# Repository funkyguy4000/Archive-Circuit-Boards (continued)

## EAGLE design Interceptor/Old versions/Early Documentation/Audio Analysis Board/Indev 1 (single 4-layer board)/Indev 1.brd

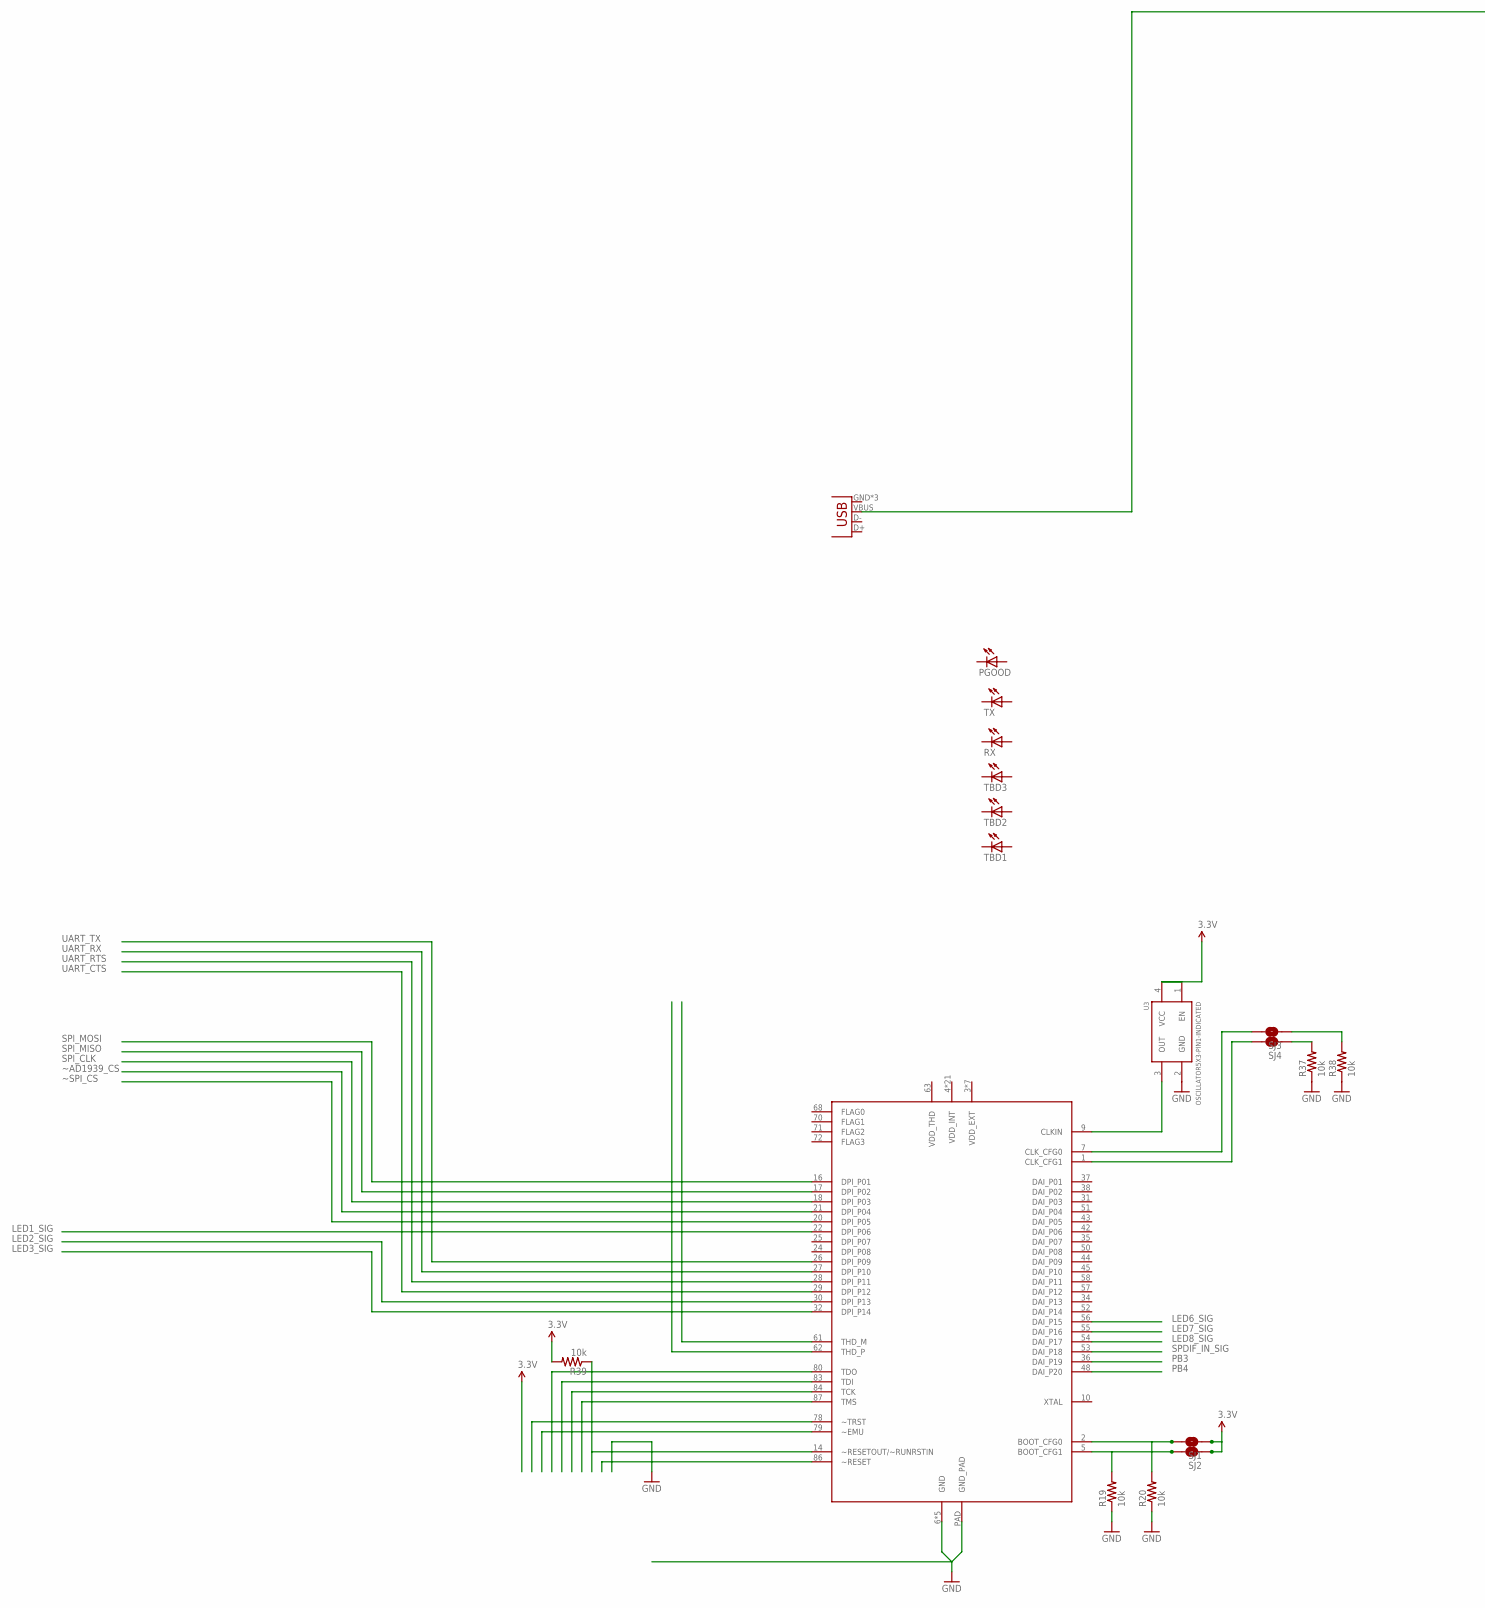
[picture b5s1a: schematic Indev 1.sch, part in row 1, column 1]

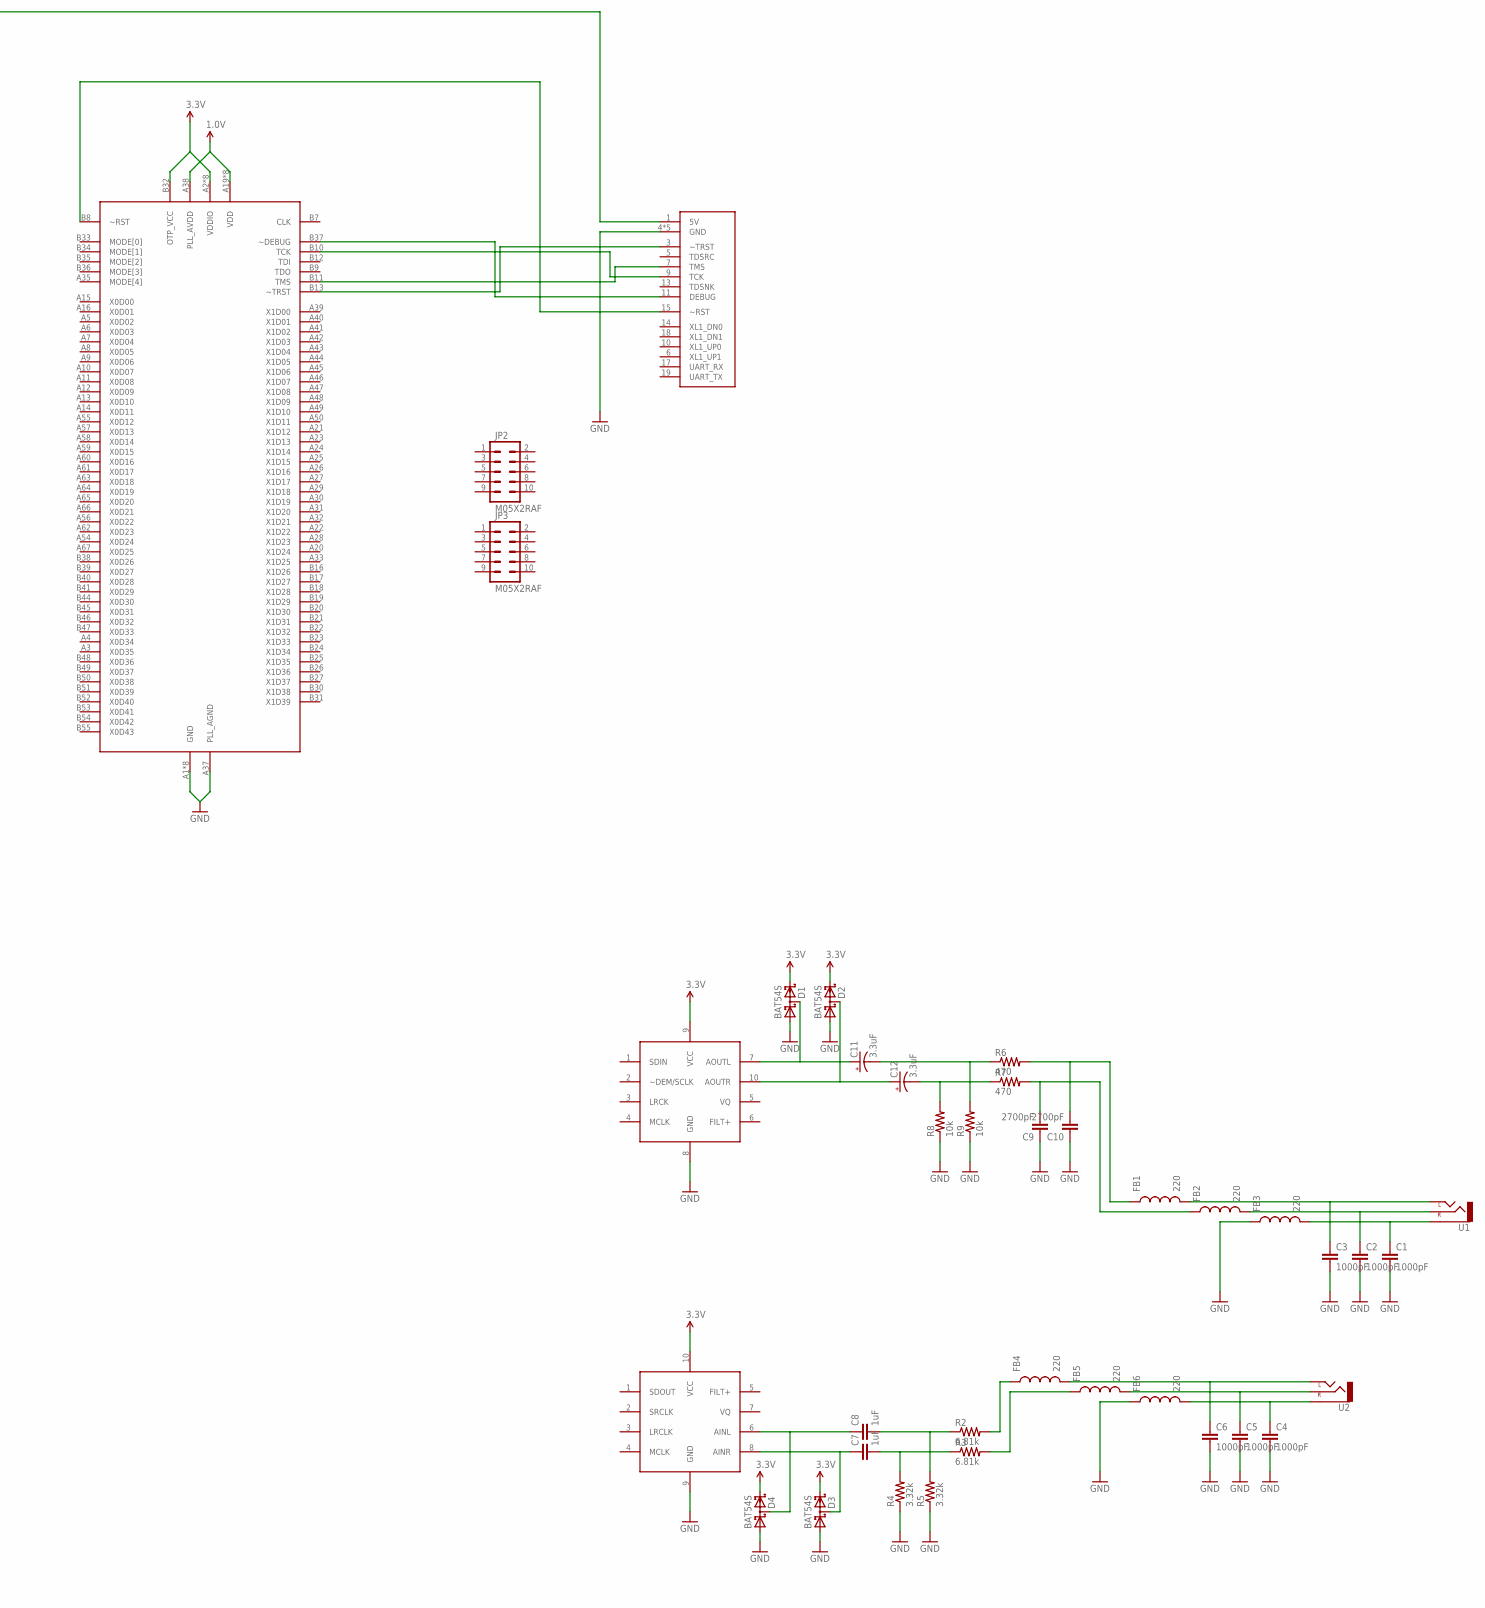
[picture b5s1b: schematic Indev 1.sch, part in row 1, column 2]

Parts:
C1, C2, C3, C4, C5, C6: 1000pF; 0402-CAP
C7, C8: 1uF; 0402-CAP
C9, C10: 2700pF; 0402-CAP
C11, C12: 3.3uF; EIA3216
D1, D2, D3, D4: BAT54S; SOT23
FB1, FB2, FB3, FB4, FB5, FB6: 220; 0805
JP1: USB-MICROB
JP2, JP3: M05X2RAF; 2X5-RAF
PGOOD: LEDCHIP-LED0603; CHIP-LED0603
R2, R3: 6.81k; 0603-RES
R4, R5: 3.32k; 0603-RES
R6, R7: 470; 0603-RES
R8, R9, R19, R20, R37, R38, R39: 10k; 0603-RES
RX: LEDCHIP-LED0603; CHIP-LED0603
SJ1, SJ2, SJ3, SJ4: SOLDERJUMPERNC; SJ_2S
TBD1, TBD2, TBD3: LEDCHIP-LED0603; CHIP-LED0603
TX: LEDCHIP-LED0603; CHIP-LED0603
U1, U2: AUDIO-JACKSMD2; AUDIO-JACK-3.5MM-SMD
U3: OSCILLATOR5X3-PIN1-INDICATED; CRYSTAL-OSC-SMD-5X3
U$1: ADSP-21479; QFN-88
U$2: CS4344-DAC; TSSOP-10
U$3: CS5343; TSSOP-10
U$4: XTAG-2; MOLEX-52745-2097
U$6: XS1-L8A-128-QF124; QFN-124

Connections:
1.0V: U$6.A19 (VDD), U$6.A34 (VDD), U$6.A38 (PLL_AVDD), U$6.A53 (VDD), U$6.A68 (VDD), U$6.B15 (VDD), U$6.B28 (VDD), U$6.B43 (VDD), U$6.B56 (VDD)
3.3V: R39.2, SJ1.1, SJ2.1, U3.1 (EN), U3.4 (VCC), U$6.A2 (VDDIO), U$6.A17 (VDDIO), U$6.A36 (VDDIO), U$6.A51 (VDDIO), U$6.B1 (VDDIO), U$6.B14 (VDDIO), U$6.B29 (VDDIO), U$6.B32 (OTP_VCC), U$6.B42 (VDDIO)
AINL: C6.1, FB4.2, U2.TIP (LEFT)
AINL_C: C8.1, D4.3 (C1A2), U$3.6 (AINL)
AINL_FB: FB4.1, R2.2
AINL_R: C8.2, R2.1, R5.2
AINR: C5.1, FB5.2, U2.RING (RIGHT)
AINR_C: C7.1, D3.3 (C1A2), U$3.8 (AINR)
AINR_FB: FB5.1, R3.2
AINR_R: C7.2, R3.1, R4.2
AIN_SLEEV: C4.1, FB6.2, U2.SLEEVE
AOUTL: C3.1, FB1.2, U1.TIP (LEFT)
AOUTL_C: C11.A (+), D1.3 (C1A2), U$2.7 (AOUTL)
AOUTL_FB: C10.2, FB1.1, R6.2
AOUTL_R: C11.C (-), R6.1, R9.2
AOUTR: C2.1, FB2.2, U1.RING (RIGHT)
AOUTR_C: C12.A (+), D2.3 (C1A2), U$2.10 (AOUTR)
AOUTR_FB: C9.2, FB2.1, R7.2
AOUTR_R: C12.C (-), R7.1, R8.2
AOUTS: C1.1, FB3.2, U1.SLEEVE
GND: C1.2, C2.2, C3.2, C4.2, C5.2, C6.2, C9.1, C10.1, D1.1 (A1), D2.1 (A1), D3.1 (A1), D4.1 (A1), FB3.1, FB6.1, R4.1, R5.1, R8.1, R9.1, R19.1, R20.1, R37.1, R38.1, U3.2 (GND), U$1.6 (GND), U$1.60 (GND), U$1.73 (GND), U$1.74 (GND), U$1.76 (GND), U$1.PAD (GND_PAD), U$2.8 (GND), U$3.9 (GND), U$4.4 (GND), U$4.8 (GND), U$4.12 (GND), U$4.16 (GND), U$4.20 (GND), U$6.A1 (GND), U$6.A18 (GND), U$6.A37 (PLL_AGND), U$6.A52 (GND), U$6.B2 (GND), U$6.B4 (GND), U$6.B5 (GND), U$6.B6 (GND), U$6.PAD (GND)
LED1_SIG: U$1.22 (DPI_P06)
LED2_SIG: U$1.30 (DPI_P13)
LED3_SIG: U$1.32 (DPI_P14)
LED6_SIG: U$1.56 (DAI_P15)
LED7_SIG: U$1.55 (DAI_P16)
LED8_SIG: U$1.54 (DAI_P17)
unnamed: JP1.VBUS, U$4.1 (5V)
unnamed: U$4.11 (DEBUG), U$6.B37 (~DEBUG)
unnamed: U3.3 (OUT), U$1.9 (CLKIN)
unnamed: U$4.9 (TCK), U$6.B10 (TCK)
unnamed: U$4.7 (TMS), U$6.B11 (TMS)
unnamed: SJ3.2, U$1.7 (CLK_CFG0)
unnamed: SJ4.2, U$1.1 (CLK_CFG1)
unnamed: R37.2, SJ4.1
unnamed: U$4.3 (~TRST), U$6.B13 (~TRST)
unnamed: R38.2, SJ3.1
unnamed: U$4.15 (~RST), U$6.B8 (~RST)
unnamed: R20.2, SJ1.2, U$1.2 (BOOT_CFG0)
unnamed: R39.1, U$1.14 (~RESETOUT/~RUNRSTIN)
unnamed: R19.2, SJ2.2, U$1.5 (BOOT_CFG1)
PB3: U$1.36 (DAI_P19)
PB4: U$1.48 (DAI_P20)
SPDIF_IN_SIG: U$1.53 (DAI_P18)
SPI_CLK: U$1.18 (DPI_P03)
SPI_MISO: U$1.17 (DPI_P02)
SPI_MOSI: U$1.16 (DPI_P01)
UART_CTS: U$1.29 (DPI_P12)
UART_RTS: U$1.28 (DPI_P11)
UART_RX: U$1.27 (DPI_P10)
UART_TX: U$1.26 (DPI_P09)
VCC: D1.2 (C2), D2.2 (C2), D3.2 (C2), D4.2 (C2), U$2.9 (VCC), U$3.10 (VCC)
~AD1939_CS: U$1.21 (DPI_P04)
~SPI_CS: U$1.20 (DPI_P05)

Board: 4 copper layers, 56 parts (8 on the bottom side), 36 nets, no tracks yet.

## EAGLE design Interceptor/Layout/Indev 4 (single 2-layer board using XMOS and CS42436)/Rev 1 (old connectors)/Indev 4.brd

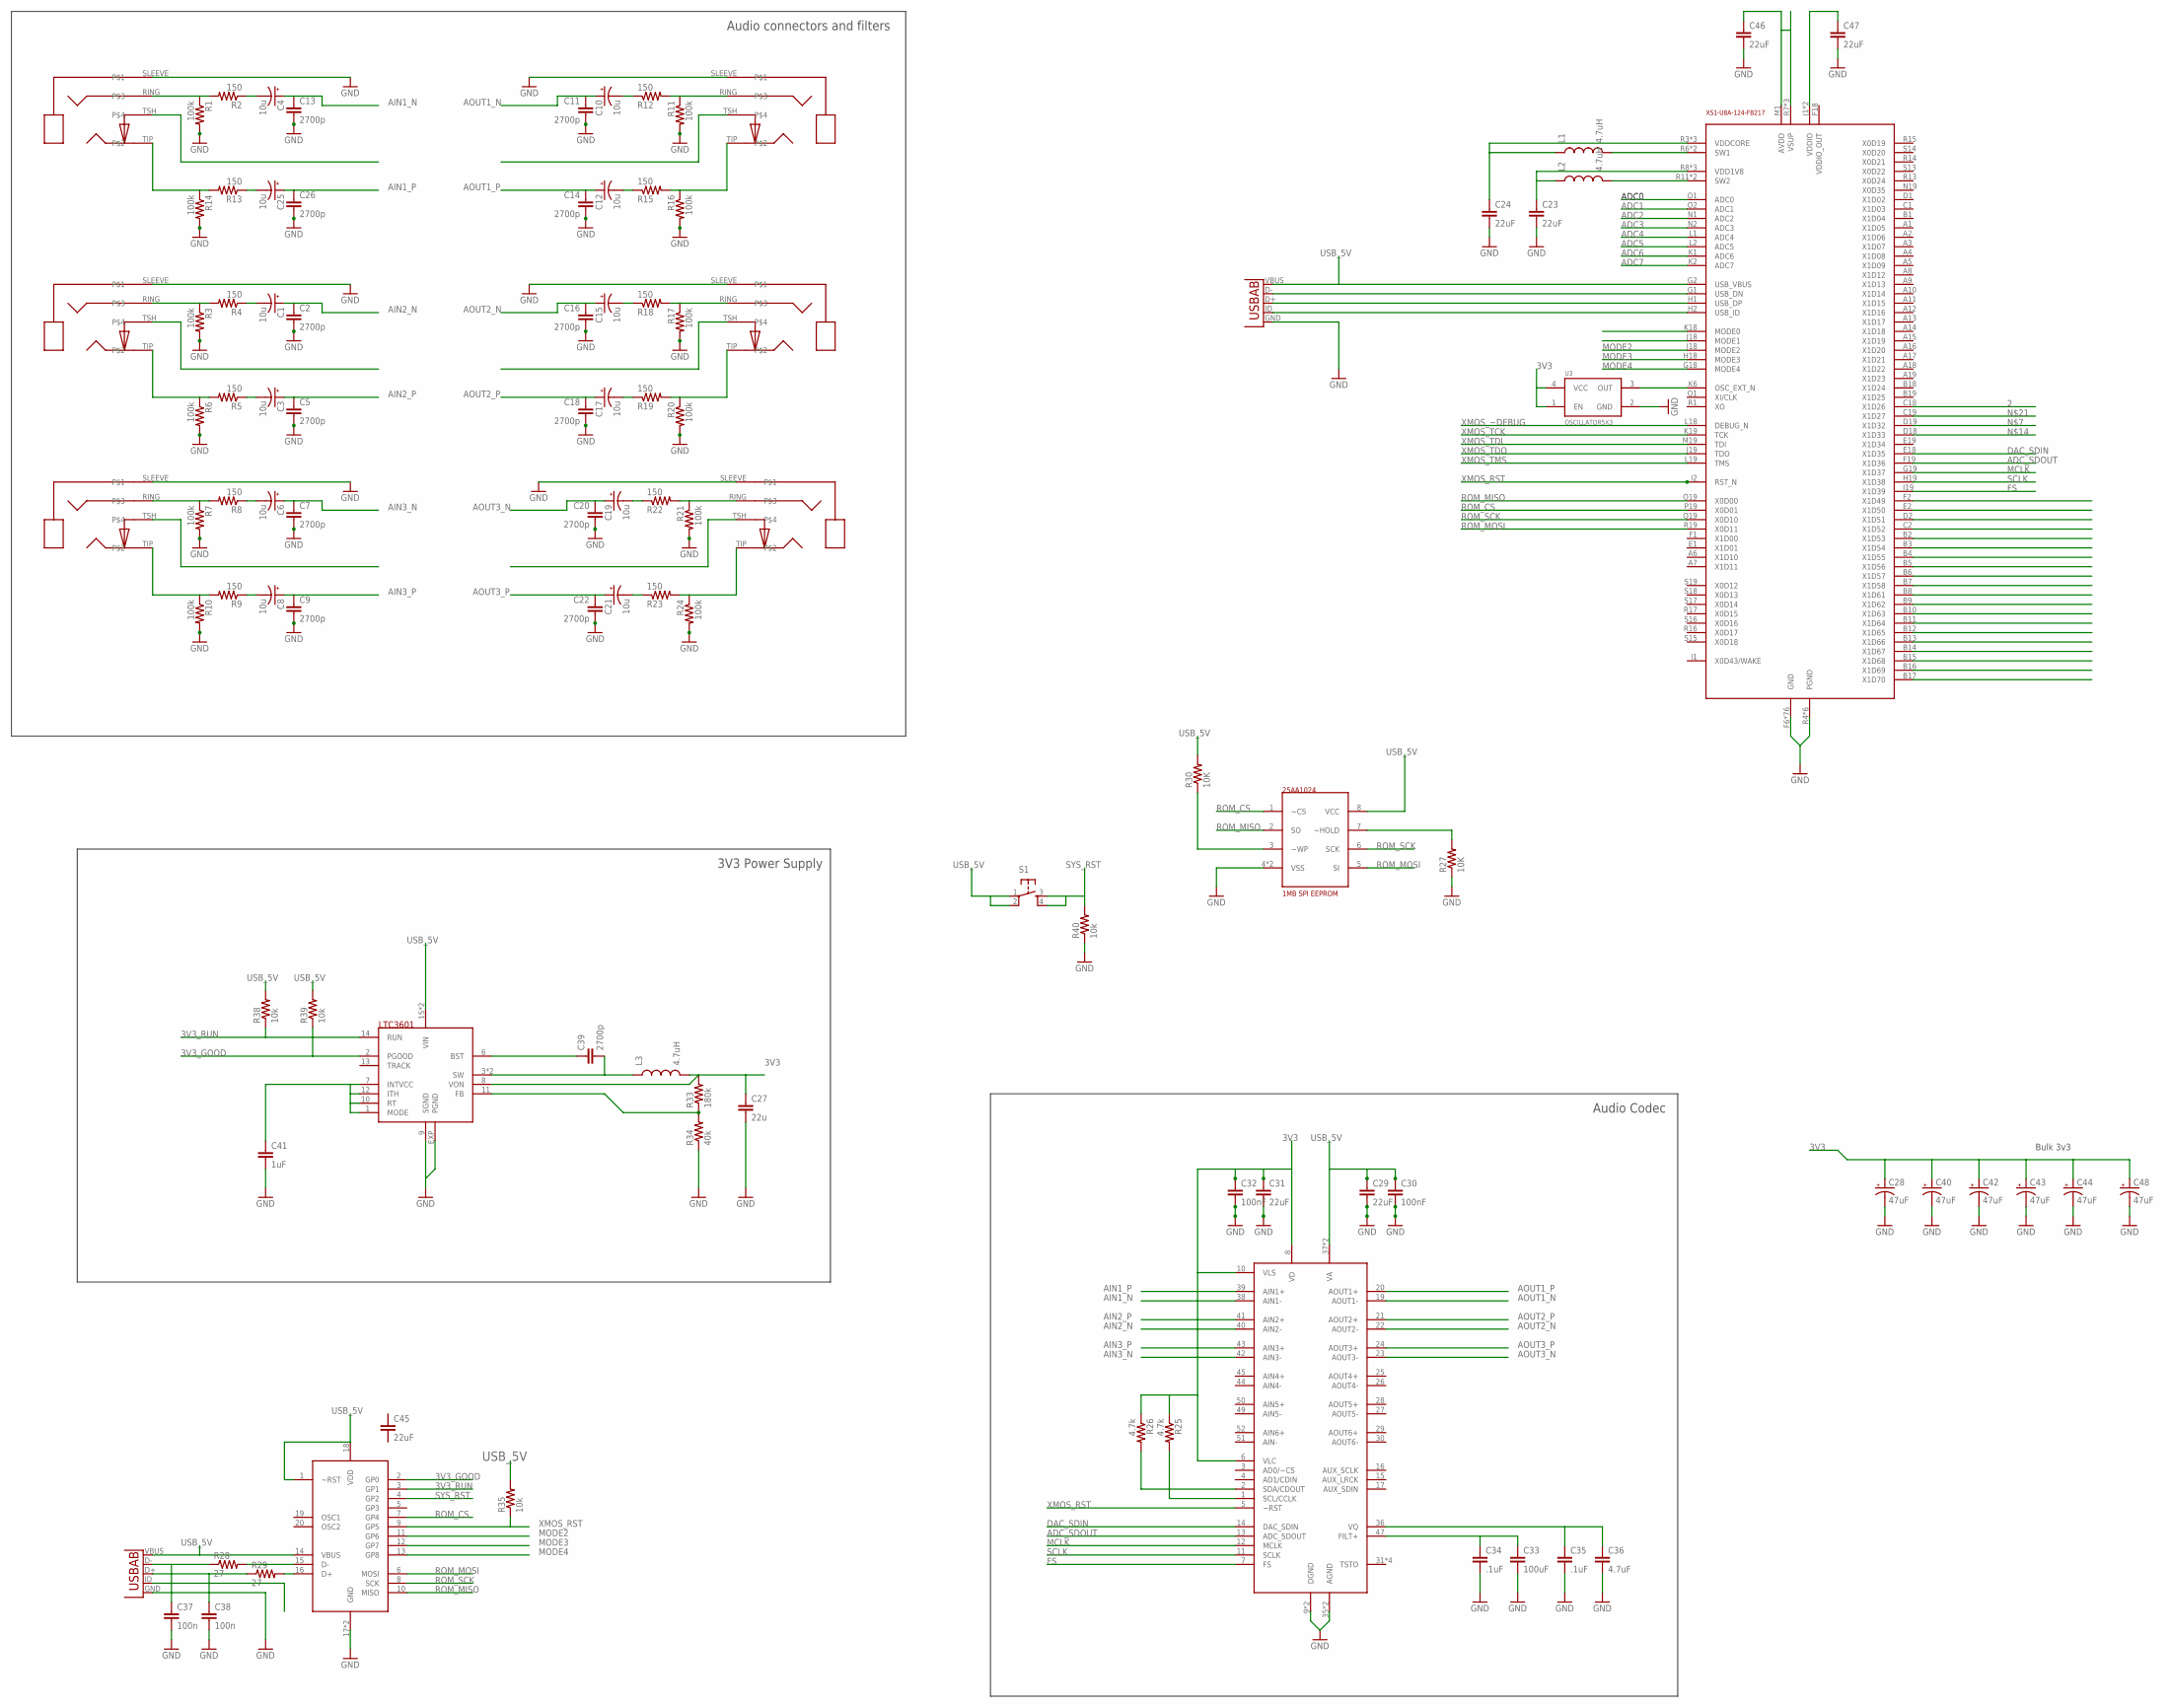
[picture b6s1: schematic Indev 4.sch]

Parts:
C1, C3, C4, C6, C8, C10, C12, C15, C17, C19, C21, C25: 10u; PANASONIC_B
C2, C5, C7, C9, C11, C13, C14, C16, C18, C20, C22, C26, C39: 2700p; 0603-CAP
C23, C24: 22uF; 0603-CAP
C27: 22u; 0603-CAP
C28, C40, C42, C43, C44, C48: 47uF; EIA3528
C29, C31, C45, C46, C47: 22uF; 0402-CAP
C30, C32: 100nF; 0402-CAP
C33: 100uF; 0402-CAP
C34, C35: .1uF; 0402-CAP
C36: 4.7uF; 0402-CAP
C37, C38: 100n; 0603-CAP
C41: 1uF; 0603-CAP
J1, J2, J3, J4, J5, J6: SJ3524_AUDIO
L1, L2, L3: 4.7uH; 1210
R1, R3, R6, R7, R10, R11, R14, R16, R17, R20, R21, R24: 100k; R0402
R2, R4, R5, R8, R9, R12, R13, R15, R18, R19, R22, R23: 150; R0402
R25, R26: 4.7k; R0402
R27, R30: 10K; R0402
R28, R29: 27; R0402
R33: 180k; R0402
R34: 40k; R0402
R35, R38, R39, R40: 10k; R0402
S1: TAC_SWITCHSMD; TACTILE_SWITCH_SMD
U1, U2: USB-AB; USB-AB-MICRO-SMD
U3: OSCILLATOR5X3; CRYSTAL-SMD-5X3
U$1: LTC3601; QFN16-3X3
U$2: 25AA1024DFN; DFN8-5X6
U$3: CS42436; QFP-52
U$4: MCP2210QFN; 20-QFN(5X5)
U$6: XS1-U8A-124-FB217; 217-BGA(.8MM)

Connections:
2: U$6.C18 (X1D26)
3V3: C27.1, C28.A (+), C31.1, C32.1, C40.A (+), C42.A (+), C43.A (+), C44.A (+), C46.1, C47.1, C48.A (+), L3.2, R25.1, R26.1, R33.2, U3.1 (EN), U3.4 (VCC), U$1.8 (VON), U$3.6 (VLC), U$3.8 (VD), U$3.10 (VLS), U$6.J1 (VDDIO), U$6.J2 (VDDIO), U$6.M1 (AVDD), U$6.R7 (VSUP), U$6.S1 (VSUP), U$6.S7 (VSUP)
3V3_GOOD: R39.1, U$1.2 (PGOOD), U$4.2 (GP0)
3V3_RUN: R38.1, U$1.14 (RUN), U$4.3 (GP1)
ADC0: U$6.O1 (ADC0)
ADC1: U$6.O2 (ADC1)
ADC2: U$6.N1 (ADC2)
ADC3: U$6.N2 (ADC3)
ADC4: U$6.L1 (ADC4)
ADC5: U$6.L2 (ADC5)
ADC6: U$6.K1 (ADC6)
ADC7: U$6.K2 (ADC7)
ADC_SDOUT: U$3.13 (ADC_SDOUT), U$6.F19 (X1D36)
AIN1_N: C4.+, C13.1, U$3.38 (AIN1-)
AIN1_P: C25.+, C26.1, U$3.39 (AIN1+)
AIN2_N: C1.+, C2.1, U$3.40 (AIN2-)
AIN2_P: C3.+, C5.1, U$3.41 (AIN2+)
AIN3_N: C6.+, C7.1, U$3.42 (AIN3-)
AIN3_P: C8.+, C9.1, U$3.43 (AIN3+)
AOUT1_N: C10.+, C11.1, U$3.19 (AOUT1-)
AOUT1_P: C12.+, C14.1, U$3.20 (AOUT1+)
AOUT2_N: C15.+, C16.1, U$3.22 (AOUT2-)
AOUT2_P: C17.+, C18.1, U$3.21 (AOUT2+)
AOUT3_N: C19.+, C20.1, U$3.23 (AOUT3-)
AOUT3_P: C21.+, C22.1, U$3.24 (AOUT3+)
CH1O_IN: J4.TSH
CH1_IN: J1.TSH
CH2O_IN: J5.TSH
CH2_IN: J2.TSH
CH3O_IN: J6.TSH
CH3_IN: J3.TSH
DAC_SDIN: U$3.14 (DAC_SDIN), U$6.E18 (X1D35)
FB: R33.1, R34.2, U$1.11 (FB)
FS: U$3.7 (FS), U$6.I19 (X1D39)
GND: C2.2, C5.2, C7.2, C9.2, C11.2, C13.2, C14.2, C16.2, C18.2, C20.2, C22.2, C23.2, C24.2, C26.2, C27.2, C28.C (-), C29.2, C30.2, C31.2, C32.2, C33.2, C34.2, C35.2, C36.2, C37.2, C38.2, C40.C (-), C41.2, C42.C (-), C43.C (-), C44.C (-), C46.2, C47.2, C48.C (-), J1.SLEEVE, J2.SLEEVE, J3.SLEEVE, J4.SLEEVE, J5.SLEEVE, J6.SLEEVE, R1.2, R3.2, R6.2, R7.2, R10.2, R11.2, R14.2, R16.2, R17.2, R20.2, R21.2, R24.2, R27.1, R34.1, R40.1, U1.GND, U2.GND, U3.2 (GND), U$1.9 (SGND), U$1.EXP (PGND), U$2.4 (VSS), U$2.PAD (VSS), U$3.9 (DGND), U$3.18 (DGND), U$3.35 (AGND), U$3.48 (AGND), U$4.17 (GND), U$4.PAD (GND), U$6.F6 (GND), U$6.F7 (GND), U$6.F8 (GND), U$6.F9 (GND), U$6.F10 (GND), U$6.F11 (GND), U$6.F12 (GND), U$6.F13 (GND), U$6.F14 (GND), U$6.G6 (GND), U$6.G7 (GND), U$6.G8 (GND), U$6.G9 (GND), U$6.G10 (GND), U$6.G11 (GND), U$6.G12 (GND), U$6.G13 (GND), U$6.G14 (GND), U$6.H6 (GND), U$6.H7 (GND), U$6.H8 (GND), U$6.H9 (GND), U$6.H10 (GND), U$6.H11 (GND), U$6.H12 (GND), U$6.H13 (GND), U$6.H14 (GND), U$6.I6 (GND), U$6.I7 (GND), U$6.I8 (GND), U$6.I9 (GND), U$6.I10 (GND), U$6.I11 (GND), U$6.I12 (GND), U$6.I13 (GND), U$6.I14 (GND), U$6.J6 (GND), U$6.J7 (GND), U$6.J8 (GND), U$6.J9 (GND), U$6.J10 (GND), U$6.J11 (GND), U$6.J12 (GND), U$6.J13 (GND), U$6.J14 (GND), U$6.K7 (GND), U$6.K8 (GND), U$6.K9 (GND), U$6.K10 (GND), U$6.K11 (GND), U$6.K12 (GND), U$6.K13 (GND), U$6.K14 (GND), U$6.L8 (GND), U$6.L9 (GND), U$6.L10 (GND), U$6.L11 (GND), U$6.L12 (GND), U$6.L13 (GND), U$6.L14 (GND), U$6.M8 (GND), U$6.M9 (GND), U$6.M10 (GND), U$6.M11 (GND), U$6.M12 (GND), U$6.M13 (GND), U$6.M14 (GND), U$6.N6 (GND), U$6.N7 (GND), U$6.N8 (GND), U$6.N9 (GND), U$6.N10 (GND), U$6.N11 (GND), U$6.N12 (GND), U$6.N13 (GND), U$6.N14 (GND), U$6.R4 (PGND), U$6.R5 (PGND), U$6.R9 (PGND), U$6.R10 (PGND), U$6.S5 (PGND), U$6.S10 (PGND)
MCLK: U$3.12 (MCLK), U$6.G19 (X1D37)
MODE2: U$4.11 (GP6), U$6.I18 (MODE2)
MODE3: U$4.12 (GP7), U$6.H18 (MODE3)
MODE4: U$4.13 (GP8), U$6.G18 (MODE4)
unnamed: J1.TIP, R13.2, R14.1
unnamed: J1.RING, R1.1, R2.2
unnamed: C4.-, R2.1
unnamed: C33.1, C34.1, U$3.47 (FILT+)
unnamed: C25.-, R13.1
unnamed: C35.1, C36.1, U$3.36 (VQ)
unnamed: J2.RING, R3.1, R4.2
unnamed: C1.-, R4.1
unnamed: J2.TIP, R5.2, R6.1
unnamed: C3.-, R5.1
unnamed: R30.1, U$2.3 (~WP)
unnamed: J3.RING, R7.1, R8.2
unnamed: C6.-, R8.1
unnamed: J3.TIP, R9.2, R10.1
unnamed: C8.-, R9.1
unnamed: C39.1, U$1.6 (BST)
unnamed: J4.RING, R11.1, R12.2
unnamed: C10.-, R12.1
unnamed: C37.1, R28.1, U1.D-
unnamed: J4.TIP, R15.2, R16.1
unnamed: C12.-, R15.1
unnamed: J5.RING, R17.1, R18.2
unnamed: C15.-, R18.1
unnamed: R25.2, U$3.1 (SCL/CCLK)
unnamed: J5.TIP, R19.2, R20.1
unnamed: C17.-, R19.1
unnamed: R26.2, U$3.2 (SDA/CDOUT)
unnamed: J6.RING, R21.1, R22.2
unnamed: C19.-, R22.1
unnamed: J6.TIP, R23.2, R24.1
unnamed: C21.-, R23.1
unnamed: C38.1, R29.1, U1.D+
unnamed: R28.2, U$4.15 (D-)
unnamed: R29.2, U$4.16 (D+)
unnamed: R27.2, U$2.7 (~HOLD)
unnamed: U3.3 (OUT), U$6.K6 (OSC_EXT_N)
unnamed: L2.2, U$6.R11 (SW2), U$6.S11 (SW2)
unnamed: L1.2, U$6.R6 (SW1), U$6.S6 (SW1)
unnamed: C23.1, L2.1, U$6.R8 (VDD1V8), U$6.S8 (VDD1V8), U$6.S9 (VDD1V8)
unnamed: C24.1, L1.1, U$6.R3 (VDDCORE), U$6.S3 (VDDCORE), U$6.S4 (VDDCORE)
ROM_CS: U$2.1 (~CS), U$4.7 (GP4), U$6.P19 (X0D01)
ROM_MISO: U$2.2 (SO), U$4.10 (MISO), U$6.O19 (X0D00)
ROM_MOSI: U$2.5 (SI), U$4.6 (MOSI), U$6.R19 (X0D11)
ROM_SCK: U$2.6 (SCK), U$4.8 (SCK), U$6.Q19 (X0D10)
SCLK: U$3.11 (SCLK), U$6.H19 (X1D38)
SW: C39.2, L3.1, U$1.3 (SW), U$1.4 (SW)
SYS_RST: R40.2, S1.3, S1.4, U$4.4 (GP2)
TRACK/SS: C41.1, U$1.1 (MODE), U$1.7 (INTVCC), U$1.10 (RT), U$1.12 (ITH)
USB_5V: C29.1, C30.1, R30.2, R35.2, R38.2, R39.2, S1.1, S1.2, U1.VBUS, U2.VBUS, U$1.15 (VIN), U$1.16 (VIN), U$2.8 (VCC), U$3.37 (VA), U$3.46 (VA), U$4.1 (~RST), U$4.14 (VBUS), U$4.18 (VDD), U$6.G2 (USB_VBUS)
XMOS_RST: R35.1, U$3.5 (~RST), U$4.9 (GP5), U$6.I2 (RST_N)
XMOS_TCK: U$6.K19 (TCK)
XMOS_TDI: U$6.M19 (TDI)
XMOS_TDO: U$6.J19 (TDO)
XMOS_TMS: U$6.L19 (TMS)
XMOS_USB_ID: U2.ID (USBID), U$6.H2 (USB_ID)
XMOS_USB_N: U2.D-, U$6.G1 (USB_DN)
XMOS_USB_P: U2.D+, U$6.H1 (USB_DP)
XMOS_~DEBUG: U$6.L18 (DEBUG_N)

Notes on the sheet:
3V3 Power Supply
Audio connectors and filters
Audio Codec
Bulk 3v3

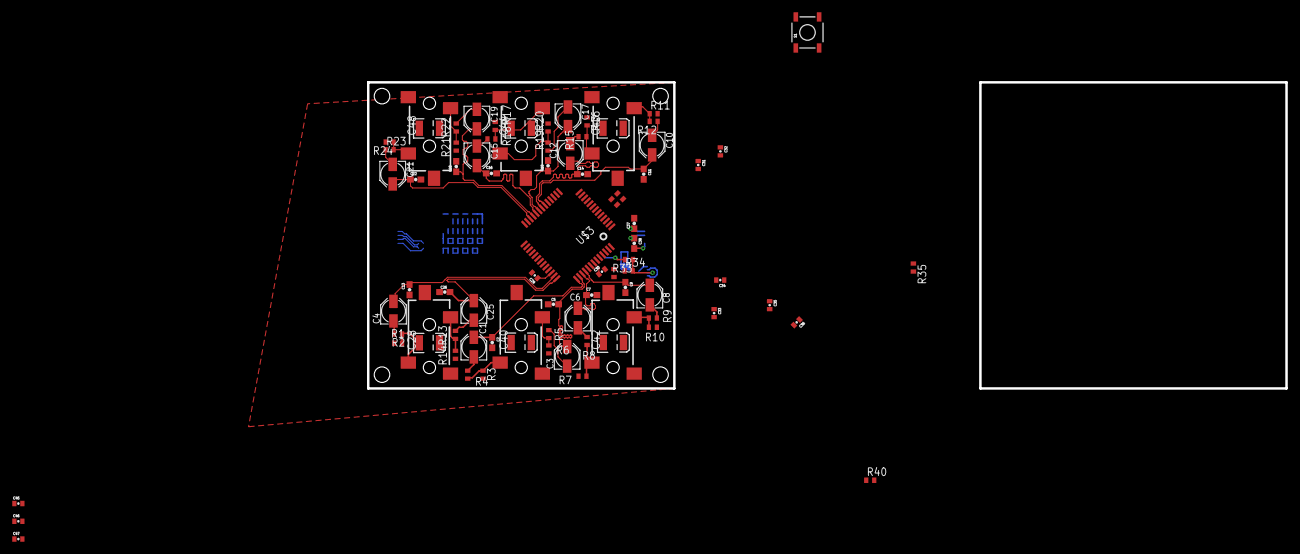
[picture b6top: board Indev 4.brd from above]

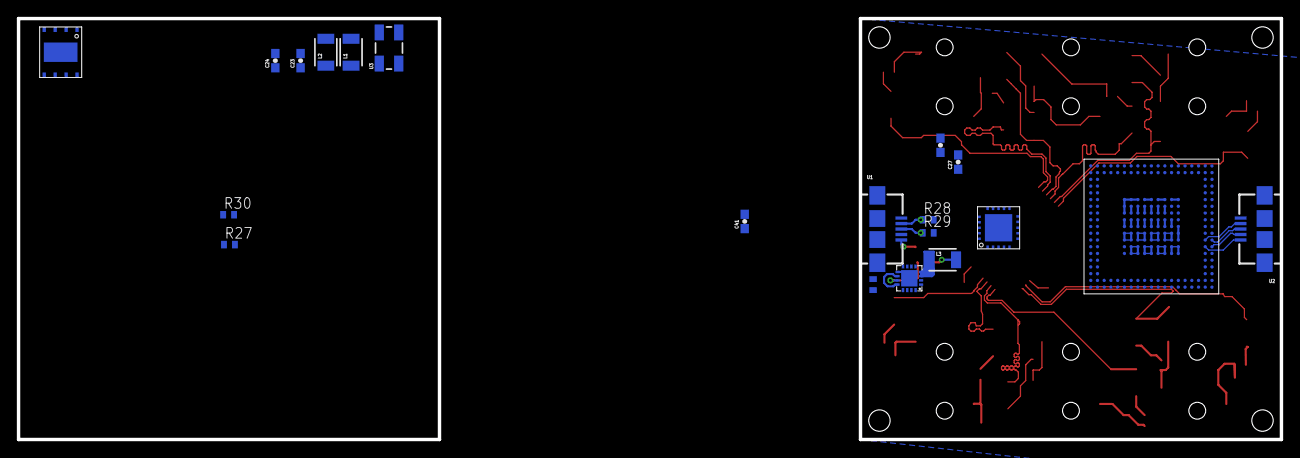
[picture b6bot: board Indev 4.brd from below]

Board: 2 copper layers, 150.0 x 50.0 mm, 102 parts (20 on the bottom side), 77 nets.

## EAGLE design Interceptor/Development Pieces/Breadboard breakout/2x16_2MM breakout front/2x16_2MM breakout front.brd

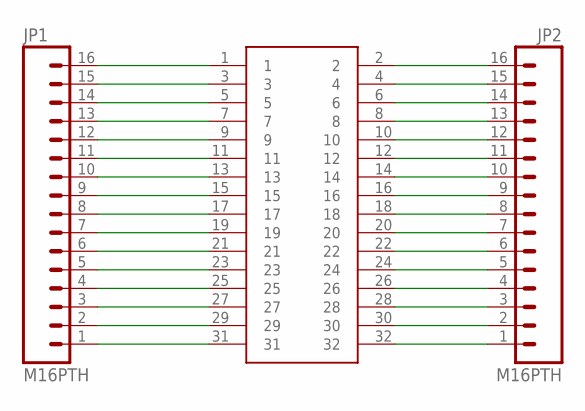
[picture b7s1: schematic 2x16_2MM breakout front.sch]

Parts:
JP1, JP2: M16PTH; 1X16
U$1: 2X16_2MM_SMD

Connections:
unnamed: JP1.16, U$1.1
unnamed: JP1.15, U$1.3
unnamed: JP1.14, U$1.5
unnamed: JP1.13, U$1.7
unnamed: JP1.12, U$1.9
unnamed: JP1.11, U$1.11
unnamed: JP1.10, U$1.13
unnamed: JP1.9, U$1.15
unnamed: JP1.8, U$1.17
unnamed: JP1.7, U$1.19
unnamed: JP1.6, U$1.21
unnamed: JP1.5, U$1.23
unnamed: JP1.4, U$1.25
unnamed: JP1.3, U$1.27
unnamed: JP1.2, U$1.29
unnamed: JP1.1, U$1.31
unnamed: JP2.1, U$1.32
unnamed: JP2.2, U$1.30
unnamed: JP2.3, U$1.28
unnamed: JP2.4, U$1.26
unnamed: JP2.5, U$1.24
unnamed: JP2.6, U$1.22
unnamed: JP2.7, U$1.20
unnamed: JP2.8, U$1.18
unnamed: JP2.9, U$1.16
unnamed: JP2.10, U$1.14
unnamed: JP2.11, U$1.12
unnamed: JP2.12, U$1.10
unnamed: JP2.13, U$1.8
unnamed: JP2.14, U$1.6
unnamed: JP2.15, U$1.4
unnamed: JP2.16, U$1.2

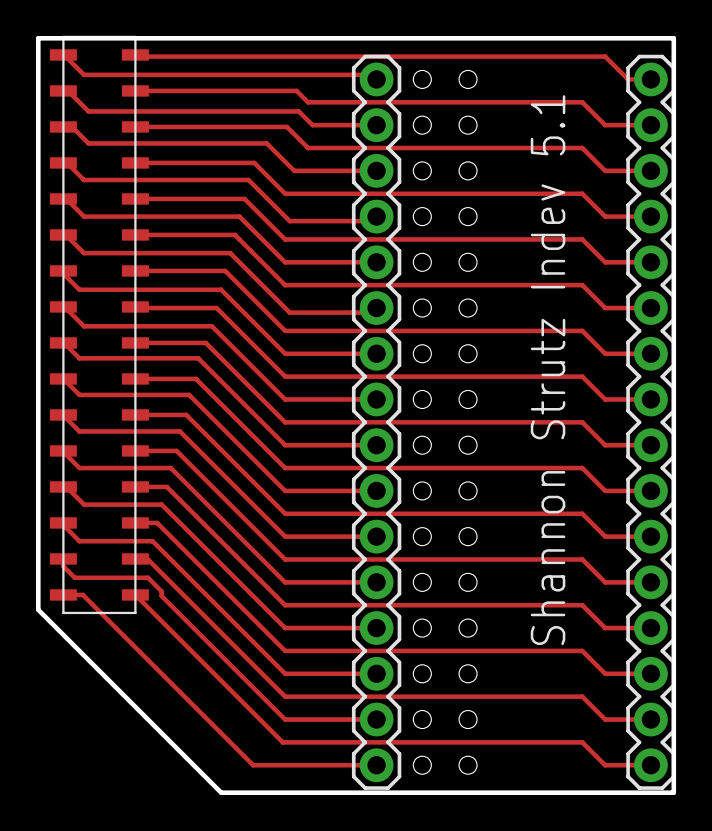
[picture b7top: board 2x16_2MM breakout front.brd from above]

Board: 2 copper layers, 35.3 x 41.9 mm, 3 parts (0 on the bottom side), 32 nets.

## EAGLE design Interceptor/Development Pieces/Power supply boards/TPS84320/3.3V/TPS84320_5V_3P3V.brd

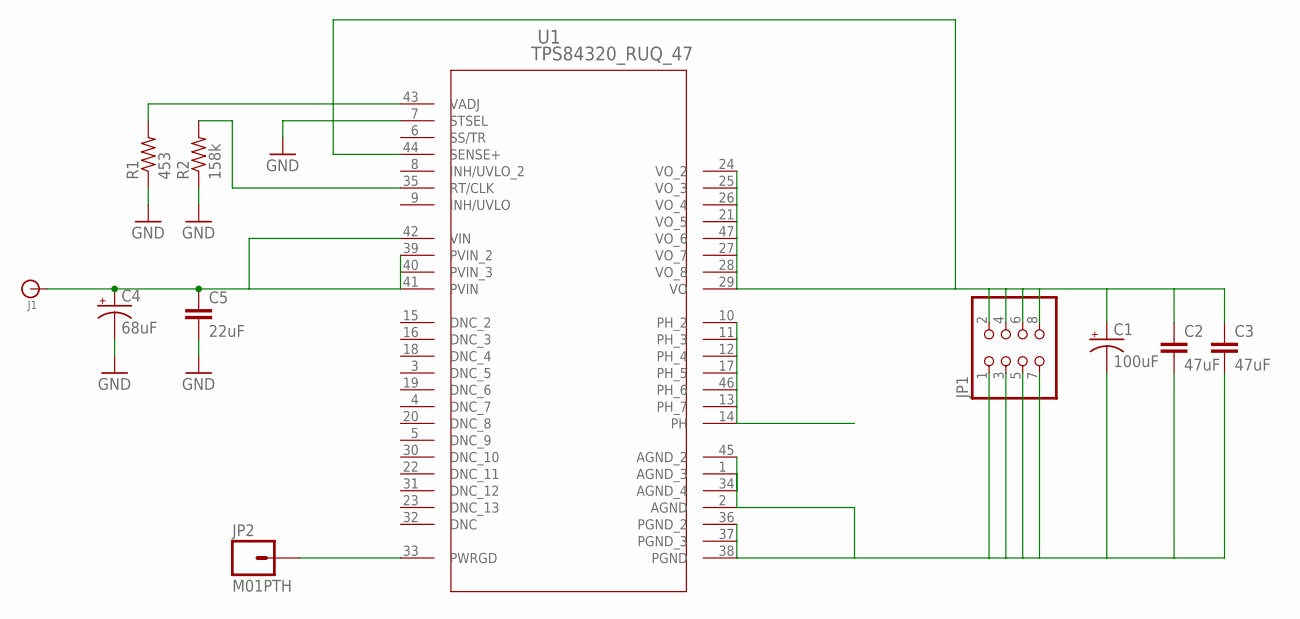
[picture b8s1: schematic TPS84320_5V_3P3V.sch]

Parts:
C1: 100uF; EIA3216
C2, C3: 47uF; 0603-CAP
C4: 68uF; EIA3216
C5: 22uF; 0603-CAP
J1: BANANA_CONN
JP1: PINHD-2X4; 2X04
JP2: M01PTH; 1X01
R1: 453; 0603-RES
R2: 158k; 0603-RES
U1: TPS84320_RUQ_47; RUQ_47

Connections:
GND: C4.C (-), C5.2, JP1.1, JP1.3, JP1.5, JP1.7, R1.1, R2.1, U1.1 (AGND_3), U1.2 (AGND), U1.7 (STSEL), U1.34 (AGND_4), U1.36 (PGND_2), U1.37 (PGND_3), U1.38 (PGND), U1.45 (AGND_2)
unnamed: JP2.1, U1.33 (PWRGD)
unnamed: U1.10 (PH_2), U1.11 (PH_3), U1.12 (PH_4), U1.13 (PH_7), U1.14 (PH), U1.17 (PH_5), U1.46 (PH_6)
unnamed: C1.A (+), C2.1, C3.1, JP1.2, JP1.4, JP1.6, JP1.8, U1.21 (VO_5), U1.24 (VO_2), U1.25 (VO_3), U1.26 (VO_4), U1.27 (VO_7), U1.28 (VO_8), U1.29 (VO), U1.44 (SENSE+), U1.47 (VO_6)
unnamed: C4.A (+), C5.1, J1.P$1, U1.39 (PVIN_2), U1.40 (PVIN_3), U1.41 (PVIN), U1.42 (VIN)
unnamed: R1.2, U1.43 (VADJ)
unnamed: R2.2, U1.35 (RT/CLK)
unnamed: C1.C (-), C2.2, C3.2

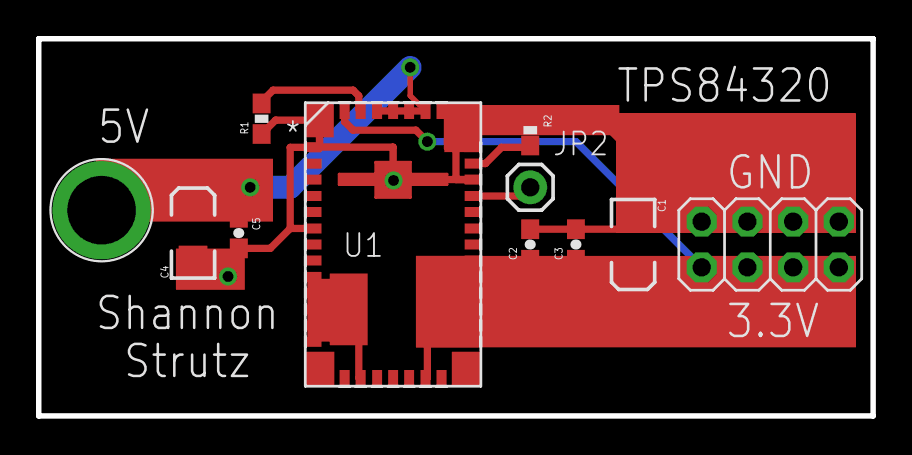
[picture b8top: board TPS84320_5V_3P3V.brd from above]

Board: 2 copper layers, 46.4 x 21.0 mm, 11 parts (0 on the bottom side), 8 nets.

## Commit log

2014-01-14 Update LICENSE
2014-01-15 Initial project upload
    Also include library.
2014-01-15 Update README.md
    Adding library list and project descriptions.
2014-01-15 Remove order files
2014-01-15 Add Pictures, edit ADSP2147x breakout, remove ALS
2014-01-15 Testing new picture sizes
2014-02-13 add IEEE resources
2014-02-13 Add workshop Schematic
2014-02-13 remove duplicate
2014-03-28 Dev board iteration + misc remove
2014-03-28 Update DAC,ADC, and ADSP
2014-10-02 Adding old audio "Interceptor" project data
    This project was meant to intercept incoming analog signals, run various
    DSP algorithms on the signals, then generate visualizations based off of
    the algorithms and would send the same analog signal back out to
    speakers.
2014-12-27 Updated readme description of parts library
2014-12-27 Update maintained library
2014-12-27 Update README.md
    Change devices to table
2014-12-29 Adding Cortex Connector library
2014-12-29 Updating cortex connector library
2014-12-29 Removing backup files
2014-12-29 removing incorrect pictures
2015-02-16 fix SMOD IO expander copper pours
2015-02-17 Updating design to next revision
